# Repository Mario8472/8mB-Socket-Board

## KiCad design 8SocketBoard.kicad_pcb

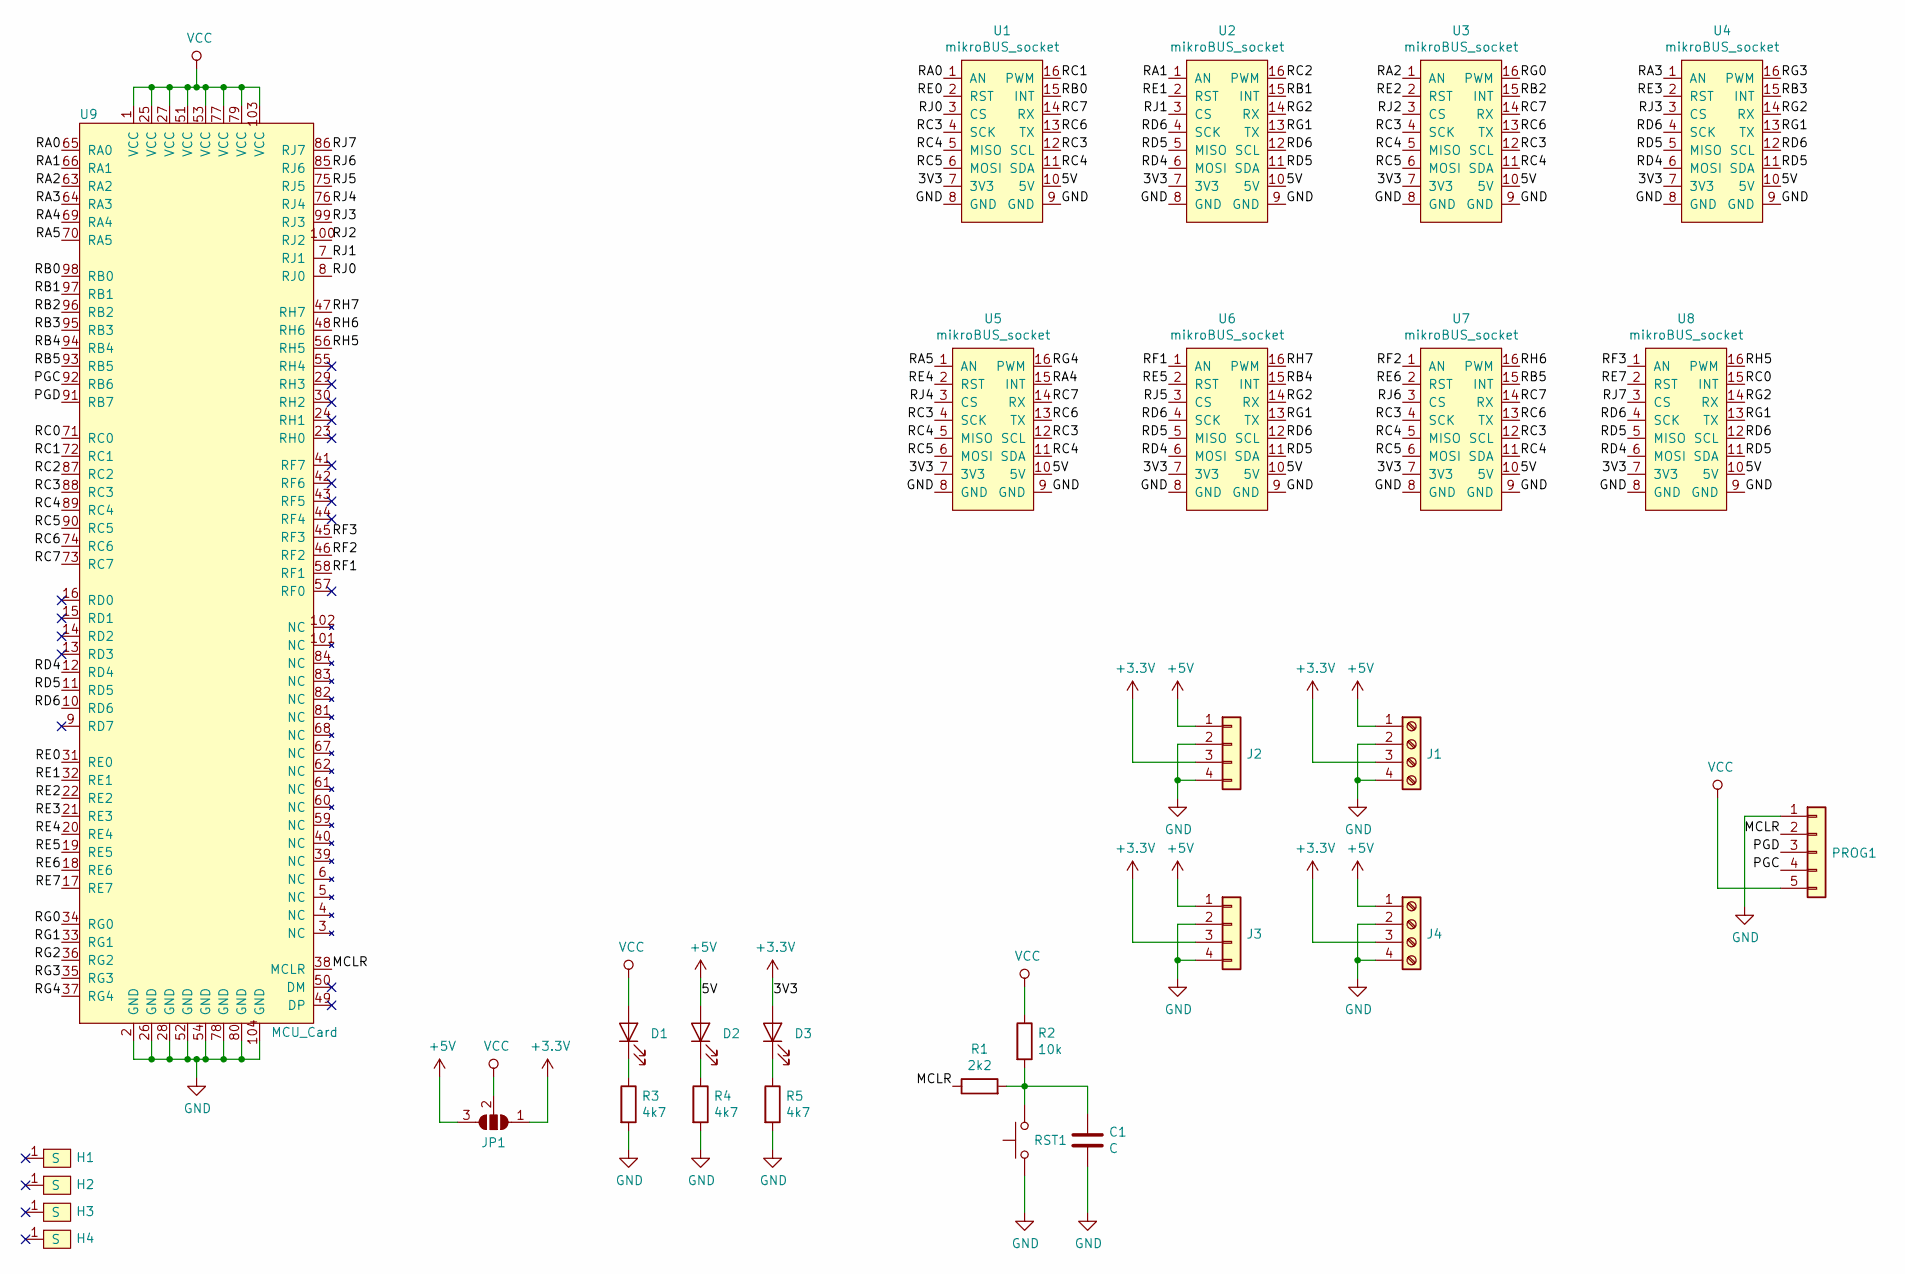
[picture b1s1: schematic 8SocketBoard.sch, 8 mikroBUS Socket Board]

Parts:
C1: C; C_0805_2012Metric
D1, D2, D3: LED; LED_0805_2012Metric
H1, H2, H3, H4: ScrewHoleM3; M3_ScrewPad
J1, J4: Screw_Terminal_01x04; PCB_Screw_Terminal_5.08_4ways
J2, J3: Conn_01x04; PinHeader_1x04_P2.54mm_Vertical
JP1: SolderJumper_3_Open; Jumper_0805
PROG1: Conn_01x05; PinHeader_1x05_P2.54mm_Vertical
R1: 2k2; R_0805_2012Metric
R2: 10k; R_0805_2012Metric
R3, R4, R5: 4k7; R_0805_2012Metric
RST1: SW_Push; TACTSWITCH6x6
U1, U2, U3, U4, U5, U6, U7, U8: mikroBUS_socket
U9: MCU_Card

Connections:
+3V3: D3.2 (A), J1.3, J2.3, J3.3, J4.3, JP1.1 (A), U1.7 (3V3), U2.7 (3V3), U3.7 (3V3), U4.7 (3V3), U5.7 (3V3), U6.7 (3V3), U7.7 (3V3), U8.7 (3V3)
+5V: D2.2 (A), J1.1, J2.1, J3.1, J4.1, JP1.3 (B), U1.10 (5V), U2.10 (5V), U3.10 (5V), U4.10 (5V), U5.10 (5V), U6.10 (5V), U7.10 (5V), U8.10 (5V)
/MCLR: PROG1.2, R1.1, U9.38 (MCLR)
/PGC: PROG1.4, U9.92 (RB6)
/PGD: PROG1.3, U9.91 (RB7)
/RA0: U1.1 (AN), U9.65 (RA0)
/RA1: U2.1 (AN), U9.66 (RA1)
/RA2: U3.1 (AN), U9.63 (RA2)
/RA3: U4.1 (AN), U9.64 (RA3)
/RA4: U5.15 (INT), U9.69 (RA4)
/RA5: U5.1 (AN), U9.70 (RA5)
/RB0: U1.15 (INT), U9.98 (RB0)
/RB1: U2.15 (INT), U9.97 (RB1)
/RB2: U3.15 (INT), U9.96 (RB2)
/RB3: U4.15 (INT), U9.95 (RB3)
/RB4: U6.15 (INT), U9.94 (RB4)
/RB5: U7.15 (INT), U9.93 (RB5)
/RC0: U8.15 (INT), U9.71 (RC0)
/RC1: U1.16 (PWM), U9.72 (RC1)
/RC2: U2.16 (PWM), U9.87 (RC2)
/RC3: U1.4 (SCK), U1.12 (SCL), U3.4 (SCK), U3.12 (SCL), U5.4 (SCK), U5.12 (SCL), U7.4 (SCK), U7.12 (SCL), U9.88 (RC3)
/RC4: U1.5 (MISO), U1.11 (SDA), U3.5 (MISO), U3.11 (SDA), U5.5 (MISO), U5.11 (SDA), U7.5 (MISO), U7.11 (SDA), U9.89 (RC4)
/RC5: U1.6 (MOSI), U3.6 (MOSI), U5.6 (MOSI), U7.6 (MOSI), U9.90 (RC5)
/RC6: U1.13 (TX), U3.13 (TX), U5.13 (TX), U7.13 (TX), U9.74 (RC6)
/RC7: U1.14 (RX), U3.14 (RX), U5.14 (RX), U7.14 (RX), U9.73 (RC7)
/RD4: U2.6 (MOSI), U4.6 (MOSI), U6.6 (MOSI), U8.6 (MOSI), U9.12 (RD4)
/RD5: U2.5 (MISO), U2.11 (SDA), U4.5 (MISO), U4.11 (SDA), U6.5 (MISO), U6.11 (SDA), U8.5 (MISO), U8.11 (SDA), U9.11 (RD5)
/RD6: U2.4 (SCK), U2.12 (SCL), U4.4 (SCK), U4.12 (SCL), U6.4 (SCK), U6.12 (SCL), U8.4 (SCK), U8.12 (SCL), U9.10 (RD6)
/RE0: U1.2 (RST), U9.31 (RE0)
/RE1: U2.2 (RST), U9.32 (RE1)
/RE2: U3.2 (RST), U9.22 (RE2)
/RE3: U4.2 (RST), U9.21 (RE3)
/RE4: U5.2 (RST), U9.20 (RE4)
/RE5: U6.2 (RST), U9.19 (RE5)
/RE6: U7.2 (RST), U9.18 (RE6)
/RE7: U8.2 (RST), U9.17 (RE7)
/RF1: U6.1 (AN), U9.58 (RF1)
/RF2: U7.1 (AN), U9.46 (RF2)
/RF3: U8.1 (AN), U9.45 (RF3)
/RG0: U3.16 (PWM), U9.34 (RG0)
/RG1: U2.13 (TX), U4.13 (TX), U6.13 (TX), U8.13 (TX), U9.33 (RG1)
/RG2: U2.14 (RX), U4.14 (RX), U6.14 (RX), U8.14 (RX), U9.36 (RG2)
/RG3: U4.16 (PWM), U9.35 (RG3)
/RG4: U5.16 (PWM), U9.37 (RG4)
/RH5: U8.16 (PWM), U9.56 (RH5)
/RH6: U7.16 (PWM), U9.48 (RH6)
/RH7: U6.16 (PWM), U9.47 (RH7)
/RJ0: U1.3 (CS), U9.8 (RJ0)
/RJ1: U2.3 (CS), U9.7 (RJ1)
/RJ2: U3.3 (CS), U9.100 (RJ2)
/RJ3: U4.3 (CS), U9.99 (RJ3)
/RJ4: U5.3 (CS), U9.76 (RJ4)
/RJ5: U6.3 (CS), U9.75 (RJ5)
/RJ6: U7.3 (CS), U9.85 (RJ6)
/RJ7: U8.3 (CS), U9.86 (RJ7)
GND: C1.2, J1.2, J1.4, J2.2, J2.4, J3.2, J3.4, J4.2, J4.4, PROG1.1, R3.2, R4.2, R5.2, RST1.1, U1.8 (GND), U1.9 (GND), U2.8 (GND), U2.9 (GND), U3.8 (GND), U3.9 (GND), U4.8 (GND), U4.9 (GND), U5.8 (GND), U5.9 (GND), U6.8 (GND), U6.9 (GND), U7.8 (GND), U7.9 (GND), U8.8 (GND), U8.9 (GND), U9.2 (GND), U9.26 (GND), U9.28 (GND), U9.52 (GND), U9.54 (GND), U9.78 (GND), U9.80 (GND), U9.104 (GND)
unnamed: C1.1, R1.2, R2.2, RST1.2
unnamed: D1.1 (K), R3.1
unnamed: D2.1 (K), R4.1
unnamed: D3.1 (K), R5.1
VCC: D1.2 (A), JP1.2 (C), PROG1.5, R2.1, U9.1 (VCC), U9.25 (VCC), U9.27 (VCC), U9.51 (VCC), U9.53 (VCC), U9.77 (VCC), U9.79 (VCC), U9.103 (VCC)

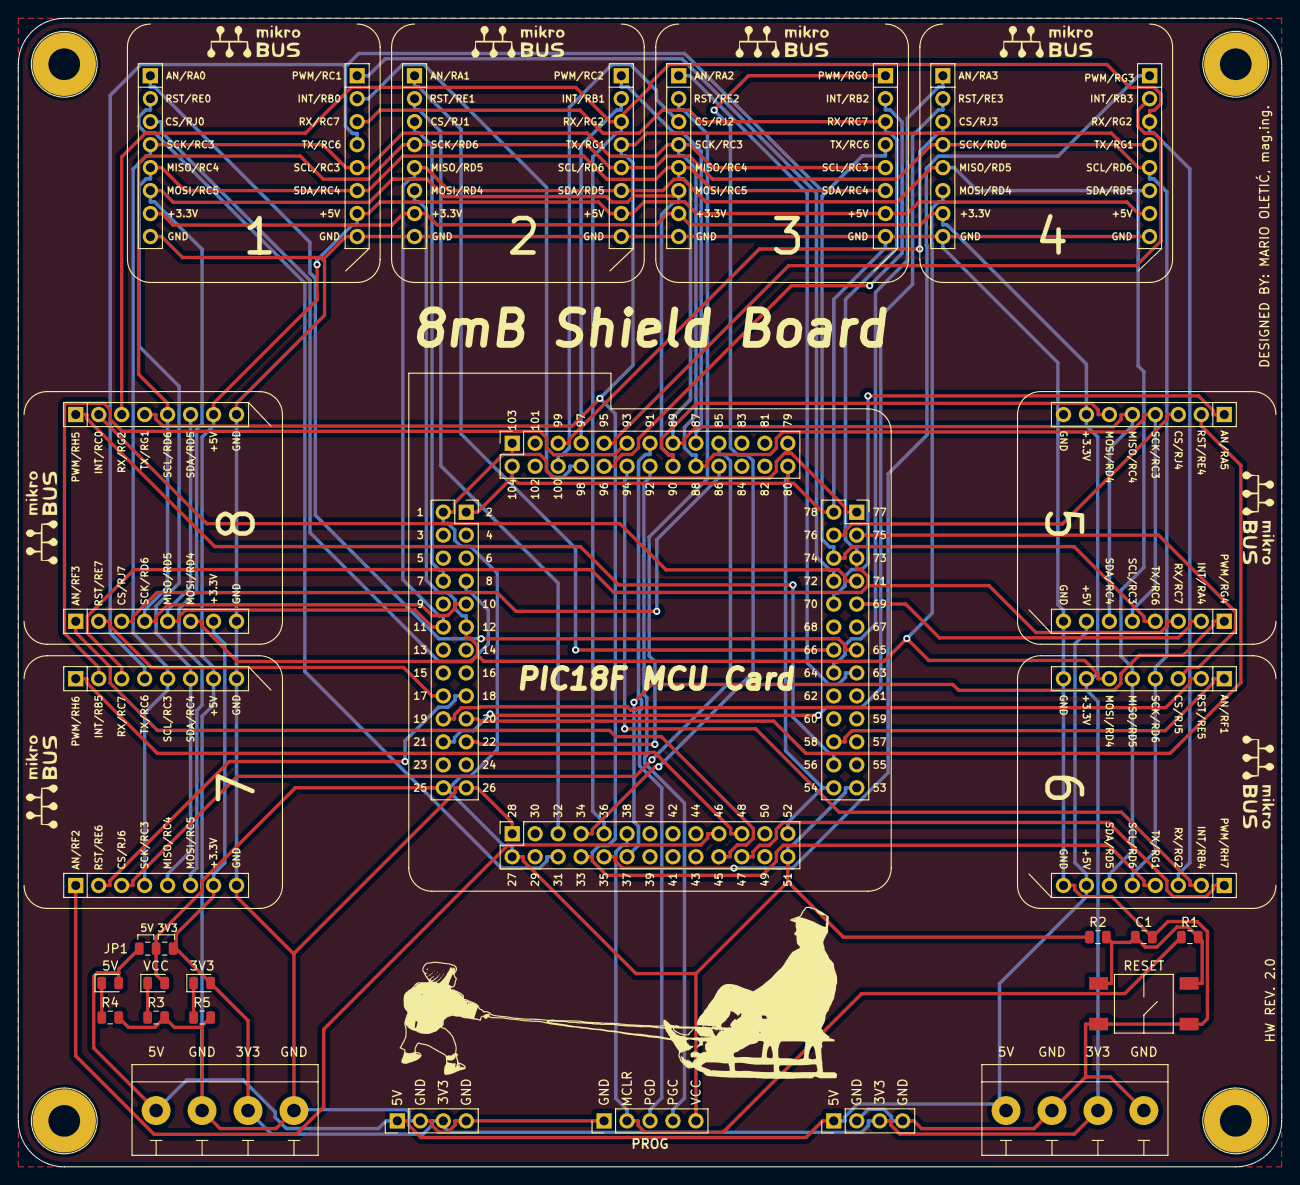
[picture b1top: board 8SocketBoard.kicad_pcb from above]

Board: 2 copper layers, 139.7 x 127.0 mm, 29 parts (0 on the bottom side), 61 nets.
